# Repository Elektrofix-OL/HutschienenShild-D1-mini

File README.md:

# HutschienenShild-D1-mini
Wemos D1 direkt in Verteilung incl. Spannungsversorgung 5V nutzen

Nach dem die App von meinem Energieversorger versagte, wollte ich meinen Haupt- und Zwischenzähler per S0 bzw. D0 auslesen können und die Daten Speicher können.
Bei Youtube konnte ich dann erfahren, wie die Daten auf einen Raspberry gespeichert, ausgewertet und angezeigt werden können. Was fehlte war die Möglichkeit einen ESP8266 direkt auf die Hutschiene zu setzten und nur noch anzuschießen.
Darum habe ich mich rangesetzt, ein Shield zu entwikeln.

# Schaltplan:

Wie zu sehen ist, ist das ganze nicht's besonderes. Aus 230V-AC werden über ein Wandler 5V-DC bereitgestellt. Der D1-Mini macht daraus seinen 3,3V und die Ein-/Ausgänge werden direkt an SV1 herausgeführt.
Auf der Leiterplatte sind für die Anschlüsse SV1-7 bis SV1-9 Pullup- und Pulldown-Widerstände möglich, wobei dort natürlich auch einen Freilaufdiode eingelötet werden können.
Auf der Unterseite sind Lötbrücken vorgesehen. So kann jeder selber entscheiden, welcher GPio von nutzen ist, da einige GPio's beim Booten des D1-Mini eine bestimmten Pegel haben müssen. Mit diesen Brücken können somit 5 digitale, oder 4 digitale und der analogen GPio's genutzt werden.
Am SV1 sind außer die 5 GPio-Zugänge noch Tx, Rx, +5V, +3,3V und GND erausgeführt. Ferne ist es möglich noch im Gehäuse ein weiteres Shild unterzubringen (sieh Foto's) 

# Gehäuse-Bilder

Wie zu sehen ist, passen die Kontakthalten nicht ganz, daher haben ich mit einem Cutter die beinden letzten Kontakthalter halbiert. Der elekrische Kontakt wird nicht beeinträchtigt.
Der Kondensator kann auch größer gewählt werden, bei mir dient er als Glättung, damit die Schaltung nicht ins Schwingen kommt.

# Bauteile
für die Bauteile habe ich eine Liste bei [www.reichelt.de](https://www.reichelt.de/my/1790195) erstellt. 

# Lizenz
Copyright (c) 2021 Elektrofix

Jeder Mensch darf das Projekt benutzen, kopieren und verändern. Der Verkauf ist jedoch verboten und auch nach der Veränderung dürfen Teile des Projekten nicht veräußert werden. Ihr habt es kostenlos bekommt, also müsst ihr die Änderungen auch Kostenlos weitergeben! Geld machen mit meinen Ideen ist nicht!

Der obige Urheberrechtshinweis und dieser Genehmigungshinweis müssen in alle Kopien oder wesentlichen Teile der Software aufgenommen werden.

Alles macht ihr aus eigenes Risiko, Haftung und Gewährleistung über nehme ich keine.

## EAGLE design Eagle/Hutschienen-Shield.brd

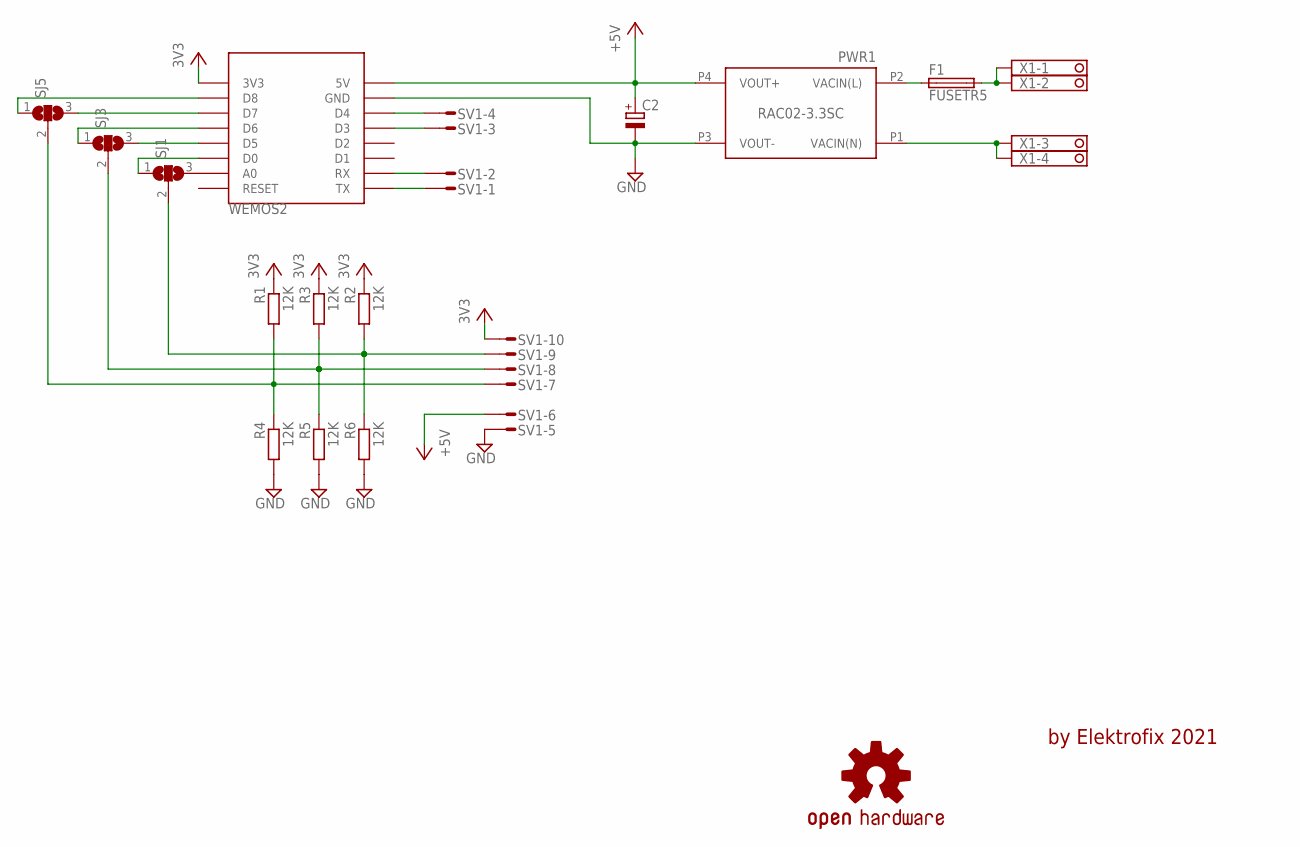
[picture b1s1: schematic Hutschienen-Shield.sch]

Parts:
C2: CPOL-EUE3.5-8; E3,5-8
F1: FUSETR5; TR5
LOGO1: OSHW-LOGOL; OSHW-LOGO-L
PWR1: RAC02-3.3SC; LOW_PROFILE_POWER_MODULE
R1, R2, R3, R4, R5, R6: 12K; 0207/12
SJ1, SJ3, SJ5: SJ2W; SJ_2
SV1: L10P
WEMOS2: WEMOS-D1-MINI
X1: 1751264

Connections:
3V3: R1.1, R2.1, R3.1, SV1.10, WEMOS2.3V3
+5V: C2.+, PWR1.P4 (VOUT+), SV1.6, WEMOS2.5V
GND: C2.-, PWR1.P3 (VOUT-), R4.2, R5.2, R6.2, SV1.5, WEMOS2.GND
unnamed: F1.1, PWR1.P2 (VACIN(L))
unnamed: F1.2, X1.1, X1.2
unnamed: PWR1.P1 (VACIN(N)), X1.3, X1.4
unnamed: SV1.4, WEMOS2.D4
unnamed: SV1.3, WEMOS2.D3
unnamed: SV1.1, WEMOS2.TX
unnamed: SV1.2, WEMOS2.RX
unnamed: SJ1.3, WEMOS2.A0
unnamed: SJ1.1, WEMOS2.D0
unnamed: SJ3.3, WEMOS2.D5
unnamed: SJ3.1, WEMOS2.D6
unnamed: SJ5.3, WEMOS2.D7
unnamed: SJ5.1, WEMOS2.D8
unnamed: R2.2, R6.1, SJ1.2, SV1.9
unnamed: R3.2, R5.1, SJ3.2, SV1.8
unnamed: R1.2, R4.1, SJ5.2, SV1.7

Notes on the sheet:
by Elektrofix 2021

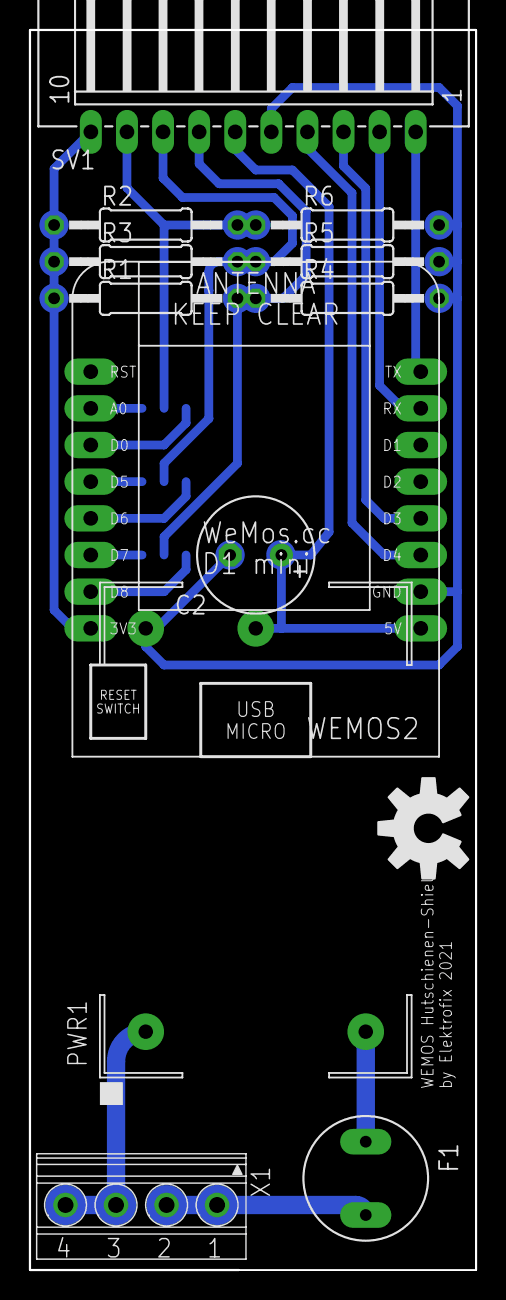
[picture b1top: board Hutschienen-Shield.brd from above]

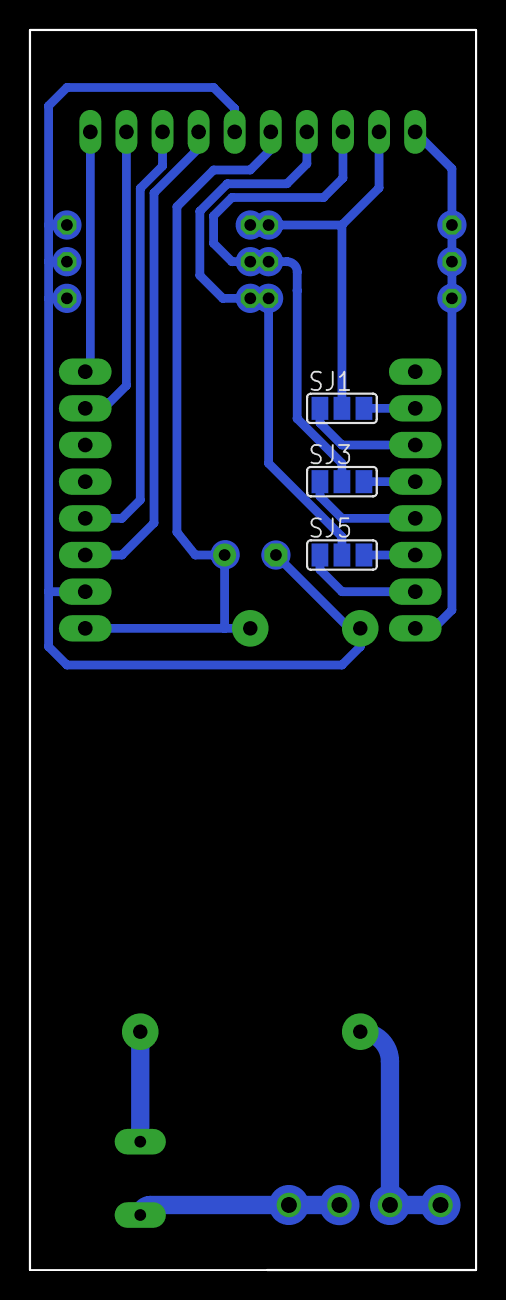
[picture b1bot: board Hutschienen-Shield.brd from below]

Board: 2 copper layers, 30.9 x 85.9 mm, 16 parts (3 on the bottom side), 19 nets.

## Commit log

2021-01-13 Create Fotos
2021-01-13 Create a

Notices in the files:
parts and their libraries:
SparkFun-Aesthetics: Licensing: Creative Commons ShareAlike 4.0 International - https://creativecommons.org/licenses/by-sa/4.0
